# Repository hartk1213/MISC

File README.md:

# MISC

This is a repo to compile all the 3d printer modifications and pcbs i have worked on with the voron discord community 
if you wanna help support me or buy a beer you can on [patreon](https://www.patreon.com/user?u=27661824&fan_landing=true) 

BTC: 3AXN2g2H9qM47EwRjAcKVZ31yz7rMHWhGx

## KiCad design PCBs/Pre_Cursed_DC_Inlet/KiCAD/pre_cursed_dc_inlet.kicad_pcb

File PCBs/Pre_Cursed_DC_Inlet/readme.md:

## Pre Cursed DC Inlet 
### NoT eVEryThiNg nEedS To Be a cUstom pCb

# BOM
| Item | Qty | Link |
| :------------: |----:| ---- |
| Power Tap Screw Terminals | 2 | [Digi-Key](https://www.digikey.com/en/products/detail/te-connectivity-amp-connectors/5055558-4/1874904)
| Barrel Jack | 1 | [Digi-Key](https://www.digikey.com/en/products/detail/cui-devices/PJ-082BH/3477156)
| M3x6 BHCS | 2 |
| M3 Heatset | 2 |

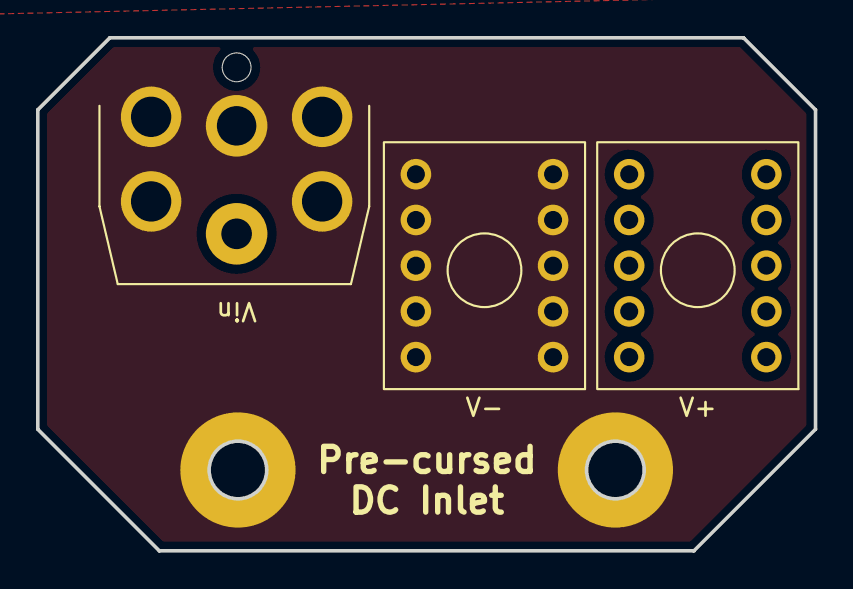
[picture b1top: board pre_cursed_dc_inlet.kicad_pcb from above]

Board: 2 copper layers, 43.2 x 28.5 mm, 3 parts (0 on the bottom side), 2 nets.

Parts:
V+: screwTerminal_MC
V-: screwTerminal_MC
Vin: PJ082BH

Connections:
V+: V+.1, Vin.1
V-: V-.1, Vin.2, Vin.MH1, Vin.MH2, Vin.MH3, Vin.MH4

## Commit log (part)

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2021-08-12 added spinner
2021-08-12 added spinner stls
2021-08-12 updated sexbolt to pissed off sexbolt
2021-08-12 added cad for mgn12 pinned and ge5c
2021-08-12 Updated Sexbolt cad
2021-08-13 updated cad and stls
2021-08-13 Adjust key height from 6.3 to 6.0 mm
2021-08-20 added image of a drive umbilical mount
2021-08-26 added write up and images for Ge5c
2021-08-26 added new image and better info
2021-09-07 Fixed table markdown and added some punctuation.
    Just some minor edits for clarity and improve the look of the read me.
2021-09-13 updated ge5c
2021-09-14 added V4 of the toolhead PCB
2021-09-14 added json files
2021-09-15 HE0 GND on TopLayer, simplified some traces
2021-09-15 Updated for 4.1
2021-09-15 Add new wiring guide for SKR 1.4
2021-09-17 Stepper wires from .5 to .9, other from 0.5 to 0.6
2021-09-18 fixed naming to 4.0 , added printed washer for 3.2
2021-09-21 added new installation picture with washers as well as ercf toolhead cover based on craxoors design
2021-09-21 added pin mod pictures
2021-09-23 added pcb covers
2021-09-26 galileo mnt for pcb
2021-09-26 updated galileo mounts
2021-09-28 Update Craxoor's vented PCB cover to work with ABBN30
2021-09-29 added LGX mount and organized files
2021-09-29 renamed files for afterburner and ABBN30
2021-10-01 removed duplicate files
2021-10-01 added ABBN cover as well as stock afterburner
2021-10-14 slicer bed models and textures
2021-11-03 Fix Hartk's Voron-Hardware link
2021-11-04 added sw files
2021-11-04 updated SW display files
2021-11-15 updated files
2021-11-15 renamed files
2021-11-29 fixed threaded adapters
2021-12-03 added voron battery bank
2021-12-03 added bom to the battery bank
2021-12-04 V0_Simple_Screen addition
2021-12-07 added v0 trident display files
2021-12-09 Update link to proper GitHub repo.
    This has moved once again, this time to the official repo.
2021-12-16 mini-M4 extruder
2021-12-16 removed m10 files
2021-12-16 updated filament path
2021-12-16 updated V0 simple display and added threaded m4
2021-12-17 fixed latch issue where it wouldnt latch when filament loaded in
2022-01-09 simple screen
2022-01-15 SB Covers
2022-01-20 simple display update
2022-01-20 Create 2
2022-01-20 fix img
2022-01-24 Update readme.md: Notes about Igus EGLM vs KGLM
2022-01-24 added new pics of mini14
2022-01-24 file organization
2022-02-12 add STL
2022-02-14 added trident pin mods, 2.4r2 pin mods for new idlers
2022-02-14 updated pin mod and y endstop with bridged counter sunk holes instead of chamfered
2022-02-14 updated Simple screen to be a direct connection to the skr mini e3 v2
2022-02-23 2.4r2 pin mod update
2022-02-23 removed files that were confusing
2022-02-24 made changes to CW1 extruder to use CW2 carriage
2022-03-06 added 1.8 pins mod, updated CW1 CW2
2022-03-07 cw1 sb
2022-03-07 removed files and redirected to hardware repo on voron design git
2022-03-20 Added Additional Variant
    Added an additional variant to annoy Nero 3d
2022-03-20 added wemos din rail mount
2022-04-05 :+1:
2022-04-06 update orientation
2022-04-14 updated gerbers and fixed a drive frame priting orientation
2022-04-14 removed files
2022-04-18 added modification for PanzerObserver mount made by Slidr
2022-04-24 uploaded 350 cad assembly
2022-04-25 organized files fixed CW1-SB-ERCF extruder body added CAD files for different extruder bodies
2022-04-25 organized skirt files/ uploaded blank skirts for 350 size
2022-04-29 uploaded 2pc toolhead board gerber files
2022-04-30 2pc board fix
2022-05-12 feat(r2-joints-print-orientation): Fixed left upper and right lower joint orientation
2022-05-15 zidler pin mod update to 5.2mm from 5.0mm
2022-05-16 2.4r2 Y endstop relocation update
2022-05-20 2pc files
2022-05-23 restored camera files
2022-05-26 added cad for all toolhead PCBs
2022-06-10 added updated display cad
2022-06-22 Updated to r2
    Updated to r2
2022-06-23 added toolhead stand
2022-07-14 Update README.md
    added information about updating an LDO kit to the SB PCB
2022-07-14 LDO PCB Update Pictures
2022-08-13 uploaded CAD for Pinned mod for lastest 2.4 and trident
2022-08-19 Added my umbilical setup i use for my v2 CAN setup
2022-08-19 added pictures
2022-08-22 Added 300 sized skirts
2022-08-22 organized files
2022-09-06 added CW2 umbilical CAD as well as file to add to fusion to make PG Threads to work with various cable glands etc...
2022-09-06 renamed folder (fixed typo)
2022-09-08 added pinout img and led pcb drilling guide and updated readme
2022-10-07 renamed pin mod to include trident parts as well , added z chian led cover, 16mm button insert and fly gemini din mounts
2022-10-07 Updated to have PG7 threaded hole
2022-10-08 Fixed file name
2022-10-17 Added skinny-Y version of umbilical to prevent inteference with Z-chains and umbilical mount on A-motor mount.
2022-10-18 Minor update to address interference with y-axis Ti backer plate
2022-12-16 various mods
2023-01-01 add v0.2 shower drain filter
2023-01-02 spool holder upload
2023-01-08 Add aux_port_example.png as example
2023-01-08 Clarification and add example
2023-01-08 Fix typos
2023-01-11 LDO -> stock
2023-01-12 Adding PG9 thread variant of the CW2 mount.
    Not printed yet, parts arrive friday.
2023-01-17 various updates to fix outstanding issues
2023-01-17 updated waveshare2.8 display
2023-01-17 added drivers that waveshare removed from their repo
2023-01-17 fixed orientation
2023-01-17 keystone skirt organization
2023-01-17 updated pictures to match latest changes
2023-01-18 added voron pcb ruler
2023-01-23 added external PSU mod
2023-01-23 added v0.2 skirt buttons
2023-01-24 pushed Fan skirts for v02
2023-01-31 remix to wiles deck panel clips
2023-02-06 umbilical mount update
2023-02-11 organized umbilical files , renamed them to be consistent naming
2023-02-13 updated waveshare 2.8 mount to fit better, in some cases the v0 door would hit the top of the display, this change has moved it down about 4mm to clear the door better
2023-02-15 Updated and consolidated umbilical mounts
2023-02-20 updated folder name
2023-02-21 updated 2.8 waveshare cover to fit better
2023-03-28 various updates
2023-04-27 Update README.md
    Added configuration for SKR Mini E3 V3
2023-05-21 Revert "various updates"
    This reverts commit 716a8121652e0a64585ce9790c2158b1d1fe6f62.
2023-09-14 fixed orientation, and names of various files
2023-09-17 G2Z_V0
2023-09-28 minisb_g2 toolhead
2023-09-28 wled_hub_case
2023-09-28 fix orientation
2023-10-04 v0_g2Z_beta_update_rev4
2023-10-09 Added miniSB_BowdenPCB
2023-10-10 renamed file
2023-11-06 updated v0 g2z drive assembly to reflect latest changes in V2/micron g2z assemblies
2023-11-27 various files pushed
2024-03-12 added V2 Zumbilical
2024-05-06 minor updates to V0 G2Z for better printablility as well as uploaded CAD files for V0 G2z and V0 chamber temp mount
2024-05-06 update to main idler body to fit chamber thermistor better
2024-05-19 Adding in the Heat set insert version for Linneo Harnesses.
2024-05-29 added Dual Nitewatch Extruder
2024-05-29 added dual nightwatch bowden extruder
2024-06-19 added bowden Y splitter to dual nightwatch, updated minisb bowden pcb cad with splitter, organized stls for dual nightwatch
2024-06-21 added a simple universal run out filament sensor
2024-07-10 added pre cursed DC inlet files
2024-07-24 Rename readm.md to readme.md
2024-07-25 uploaded miniSB G2 CAD, added one piece guidlers/shuttles for dual nightwatch
2024-08-12 added nh36 mount and fan cover
2024-08-24 nitehawk36 mount for LGX-Lite
    nitehawk36 mount for LGX-Lite
2024-09-28 nightwatch update
2024-11-10 v0 panelclip changes
2024-11-10 updated parametric wago generator
2024-11-25 Create STLs
2024-12-23 fixed minor alignment issue with the switch screw relief holes on the main housing for dual nightwatch
2025-01-10 Add file via upload
    Reworked sketch for dimensions of the 221 Wago with the bigger AWG 20-10 range (current was Wago 221 AWG 24-12)
2025-01-21 Update README.md
    Fixed incorrect stash merge
2025-01-21 fix: Pin mod image link
2025-03-13 pushed 5kg nightowl mod to repo
2025-06-12 Update filament_loading.cfg
    moved low temp check to before the first extrude move
2025-10-28 updated image
2025-11-06 v0 live idlers and v2 bentsheet z joints
2025-11-12 update to belt clamp to not stress the 9mm belt in a 90deg sharp corner when it gets clamped down
